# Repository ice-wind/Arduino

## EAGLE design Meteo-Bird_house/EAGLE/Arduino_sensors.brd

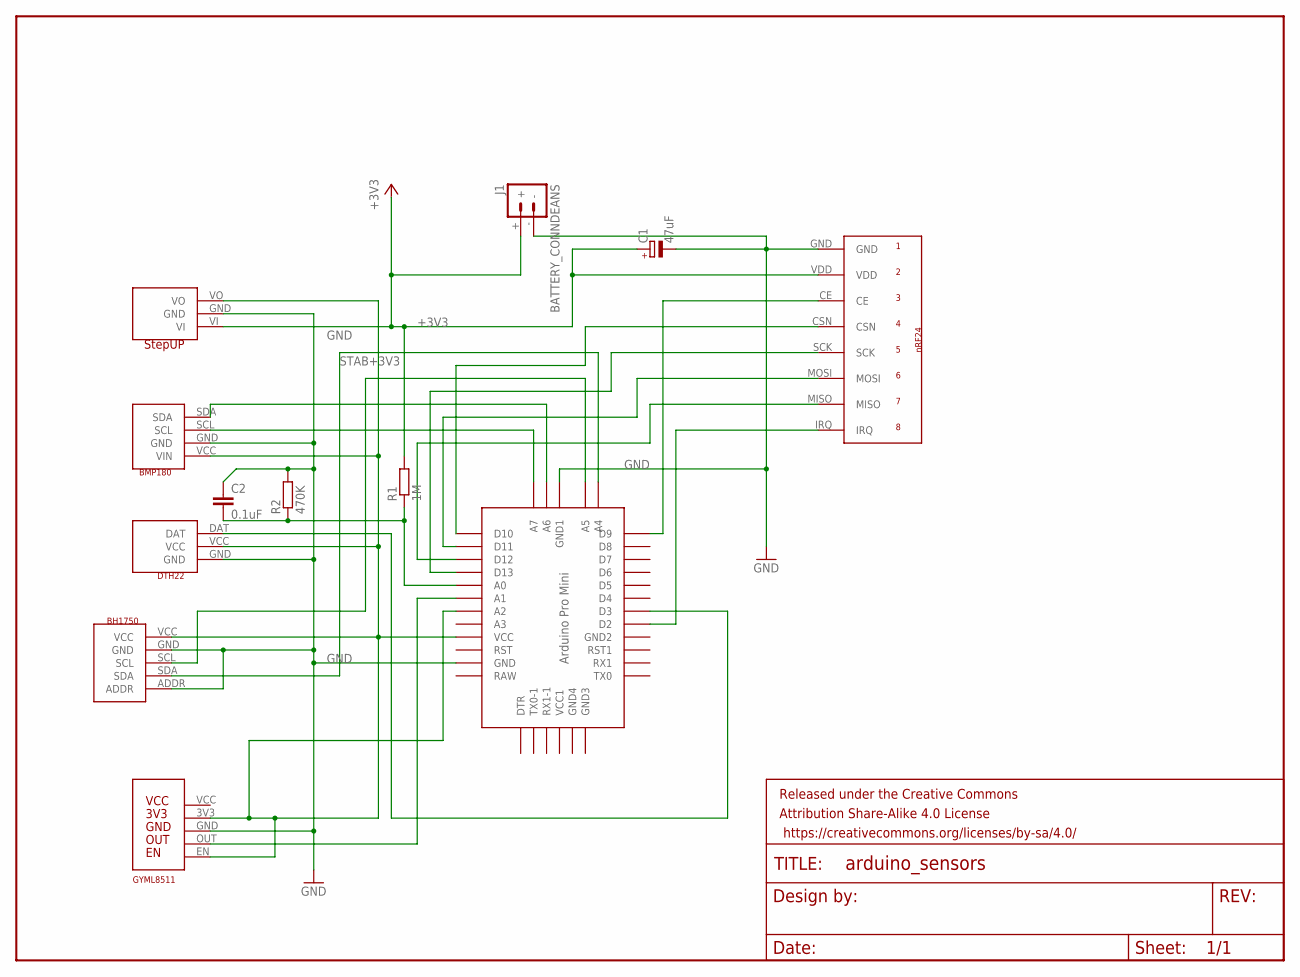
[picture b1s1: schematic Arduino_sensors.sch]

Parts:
ARDUINO_MINI: ABK-PRO-MINI
BH1: BH1750
BMP1: BMP180
C1: 47uF; E2,5-6
C2: 0.1uF; C025-025X050
DTH1: DTH22; DHT22
FRAME1: FRAME-LETTER; CREATIVE_COMMONS
J1: BATTERY_CONNDEANS; DEANS
R1: 1M; 0207/7
R2: 470K; 0207/7
STEPUP1: STEPUP
U$1: GY8511UV_SNR; GYML8511
U$2: NRF24

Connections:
+3V3: C1.+, J1.+, R1.2, STEPUP1.VI, U$2.VDD
GND: ARDUINO_MINI.GND, ARDUINO_MINI.GND4 (GND1), BH1.ADDR, BH1.GND, BMP1.GND, C1.-, C2.1, DTH1.GND, J1.-, R2.2, STEPUP1.GND, U$1.GND, U$2.GND
unnamed: ARDUINO_MINI.D3, DTH1.DAT
unnamed: ARDUINO_MINI.A1, U$1.OUT
unnamed: ARDUINO_MINI.D9, U$2.CE
unnamed: ARDUINO_MINI.D10, U$2.CSN
unnamed: ARDUINO_MINI.D13, U$2.SCK
unnamed: ARDUINO_MINI.D11, U$2.MOSI
unnamed: ARDUINO_MINI.D2, U$2.IRQ
unnamed: ARDUINO_MINI.D12, U$2.MISO
unnamed: ARDUINO_MINI.A6, BMP1.SDA
unnamed: ARDUINO_MINI.A7, BMP1.SCL
unnamed: ARDUINO_MINI.A5, BH1.SCL
unnamed: ARDUINO_MINI.A4, BH1.SDA
unnamed: ARDUINO_MINI.A0, C2.2, R1.1, R2.1
STAB+3V3: ARDUINO_MINI.A2, ARDUINO_MINI.VCC, BH1.VCC, BMP1.VCC (VIN), DTH1.VCC, STEPUP1.VO, U$1.3V3, U$1.EN

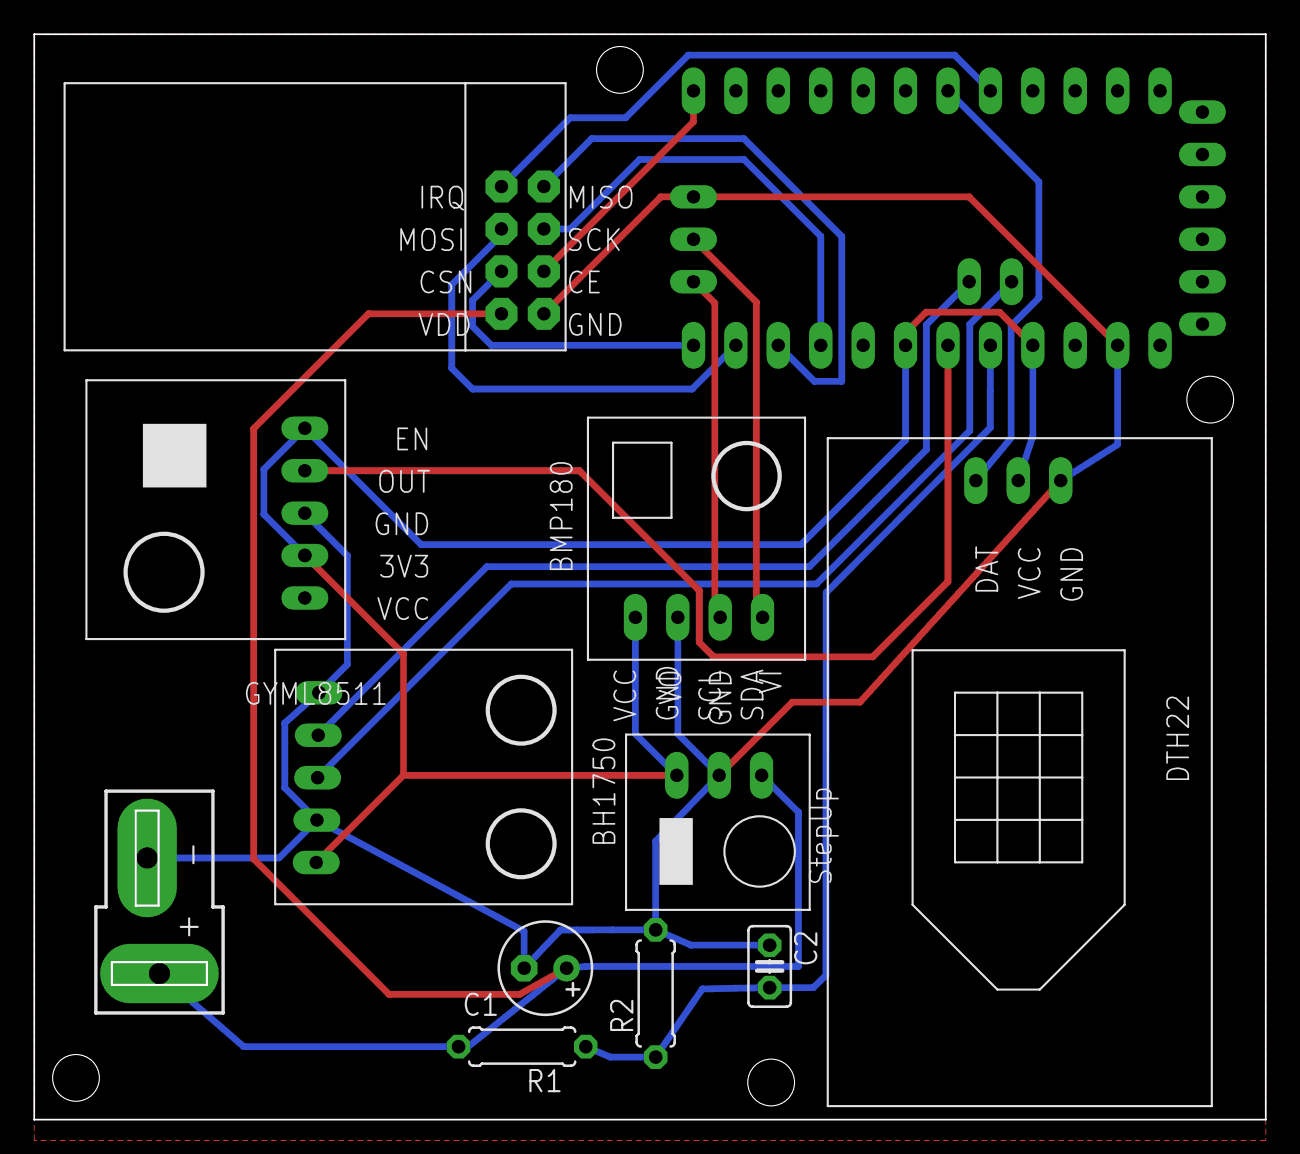
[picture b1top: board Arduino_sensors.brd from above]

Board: 2 copper layers, 73.7 x 65.0 mm, 14 parts (0 on the bottom side), 16 nets.

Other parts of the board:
DRILEGEND: DRILEGEND

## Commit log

2016-06-07 Create new Arduino repository

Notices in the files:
parts and their libraries:
SparkFun-Aesthetics: Licensing: Creative Commons ShareAlike 4.0 International - https://creativecommons.org/licenses/by-sa/4.0
SparkFun-Aesthetics: Released under the Creative Commons Attribution Share-Alike 4.0 License
SparkFun-Aesthetics: https://creativecommons.org/licenses/by-sa/4.0
